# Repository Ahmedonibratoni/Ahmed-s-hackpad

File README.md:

# Ahmed-s-hackpad
My first project. I want to make a macro pad with 6 keys, a rotary encoder for controlling the volume, and 2 LEDs for indicating if volume is turned down to 0 and if the device is turned on
Case for it will be a plain box with no top, because I don't want case at all, but for the requirements i needed to make something.
User will be able to change macro for each key directly in the code that will be flashed to the device when changes are made.
The firmware is not in its final stage, but it will be similar to what it is now, probably with some tweaks because I wasn't able to test it...

BOM was extracted directly from KiCAD
| Id | Designator                   | Footprint                                      | Quantity | Designation            | Supplier and ref|
|----|------------------------------|------------------------------------------------|----------|------------------------|-----------------|
| 1  | SW7                          | RotaryEncoder_Alps_EC11E-Switch_Vertical_H20mm | 1        | RotaryEncoder_Switch   |                 |
| 2  | SW6,SW2,SW4,SW3,SW5,SW1      | SW_Cherry_MX_1.00u_PCB                         | 6        | SW_Push                |                 |
| 3  | D2,D1                        | LED_SK6812MINI_PLCC4_3.5x3.5mm_P1.75mm         | 2        | SK6812MINI             |                 |
| 4  | U1                           | XIAO-RP2040-DIP                                | 1        | XIAO-RP2040-DIP        |                 |

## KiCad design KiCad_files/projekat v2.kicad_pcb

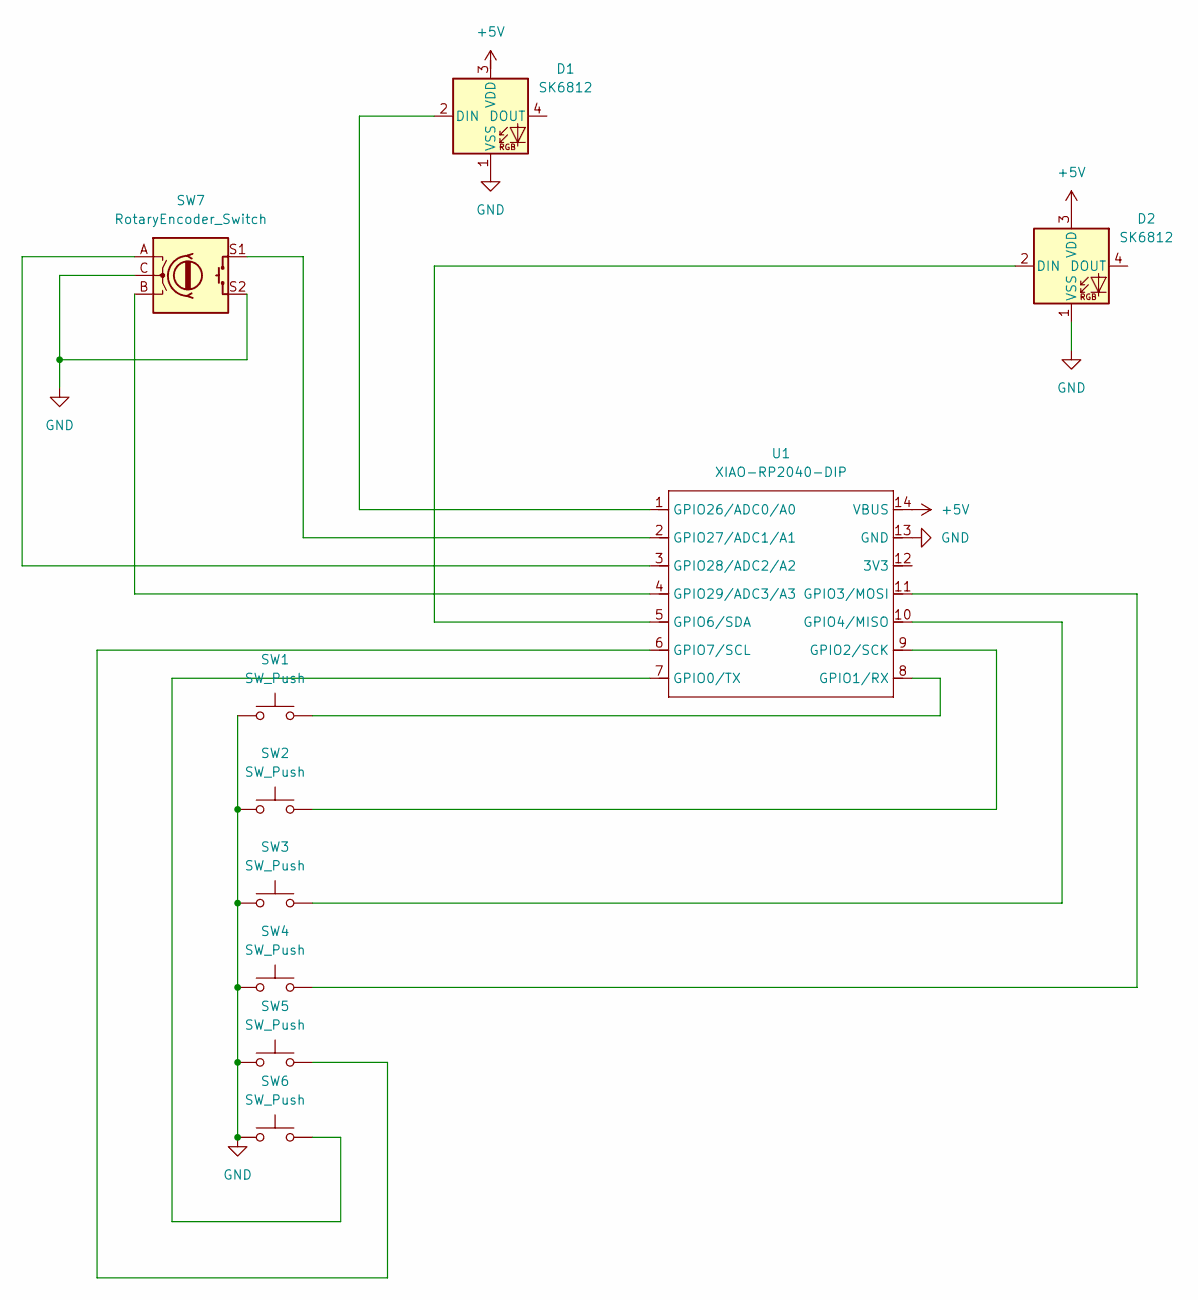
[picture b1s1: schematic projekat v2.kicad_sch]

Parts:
D1, D2: SK6812; LED_SK6812MINI_PLCC4_3.5x3.5mm_P1.75mm
SW1, SW2, SW3, SW4, SW5, SW6: SW_Push; SW_Cherry_MX_1.00u_PCB
SW7: RotaryEncoder_Switch; RotaryEncoder_Alps_EC11E_Vertical_H20mm
U1: XIAO-RP2040-DIP

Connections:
+5V: D2.3 (VDD), U1.14 (VBUS)
GND: D1.1 (VSS), D2.1 (VSS), SW1.1, SW2.1, SW3.1, SW4.1, SW5.1, SW6.1, SW7.C, SW7.S2, U1.13 (GND)
unnamed: D1.2 (DIN), U1.1 (GPIO26/ADC0/A0)
unnamed: D2.2 (DIN), U1.5 (GPIO6/SDA)
unnamed: SW6.2, U1.7 (GPIO0/TX)
unnamed: SW1.2, U1.8 (GPIO1/RX)
unnamed: SW2.2, U1.9 (GPIO2/SCK)
unnamed: SW4.2, U1.11 (GPIO3/MOSI)
unnamed: SW3.2, U1.10 (GPIO4/MISO)
unnamed: SW5.2, U1.6 (GPIO7/SCL)
unnamed: SW7.S1, U1.2 (GPIO27/ADC1/A1)
unnamed: SW7.A, U1.3 (GPIO28/ADC2/A2)
unnamed: SW7.B, U1.4 (GPIO29/ADC3/A3)

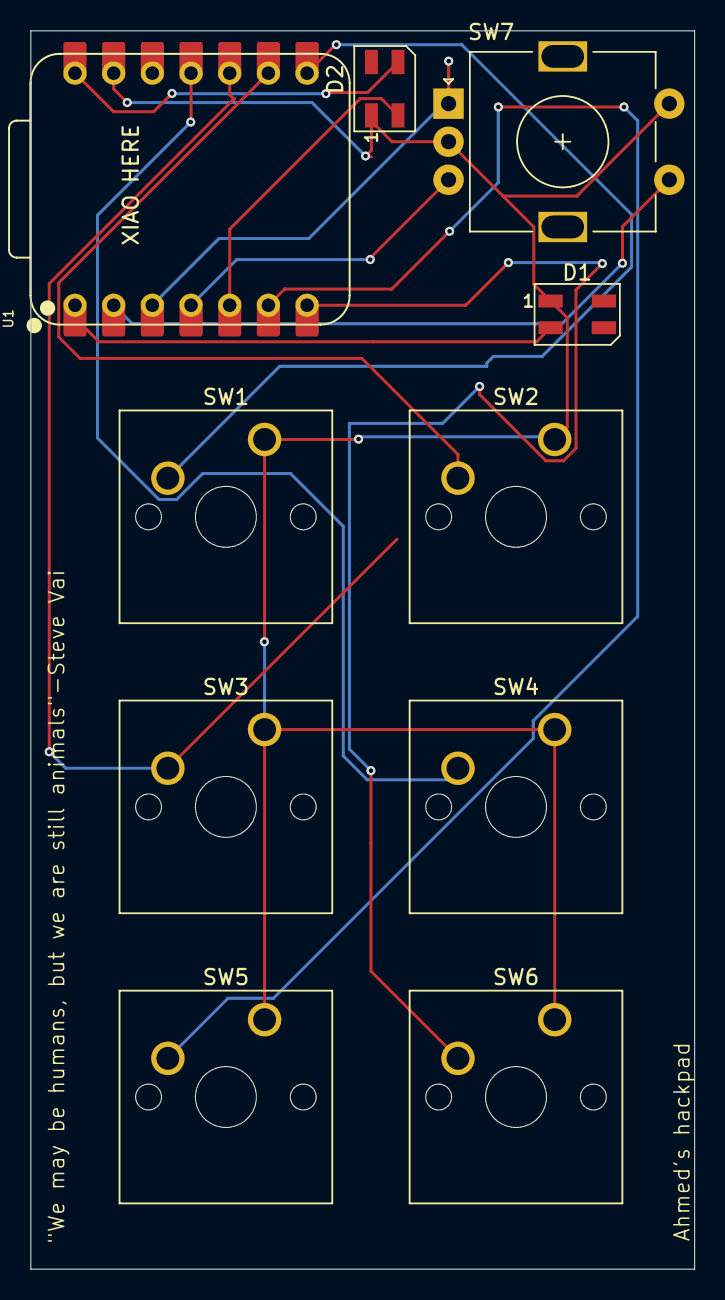
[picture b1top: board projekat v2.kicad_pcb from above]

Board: 2 copper layers, 43.6 x 81.3 mm, 10 parts (0 on the bottom side), 13 nets.

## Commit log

2026-03-07 Create folder
2026-03-07 Rename fp-info-cache to KiCad_files/fp-info-cache
2026-03-07 Update and rename fp-lib-table to KiCad_files/fp-lib-table
2026-03-07 Rename projekat v2.kicad_prl to KiCad_files/projekat v2.kicad_prl
2026-03-07 Rename projekat v2.kicad_pro to KiCad_files/projekat v2.kicad_pro
2026-03-07 Update and rename sym-lib-table to KiCad_files/sym-lib-table
2026-03-07 Rename projekat v2.step to 3Dmodels/projekat v2.step
2026-03-07 Rename Screenshot 2026-03-06 132009.png to Screenshots/Screenshot 2026-03-06 132009.png
2026-03-07 Rename Screenshot 2026-03-06 132025.png to Screenshots/Screenshot 2026-03-06 132025.png
2026-03-07 Rename rules.mk to Firmware/rules.mk
